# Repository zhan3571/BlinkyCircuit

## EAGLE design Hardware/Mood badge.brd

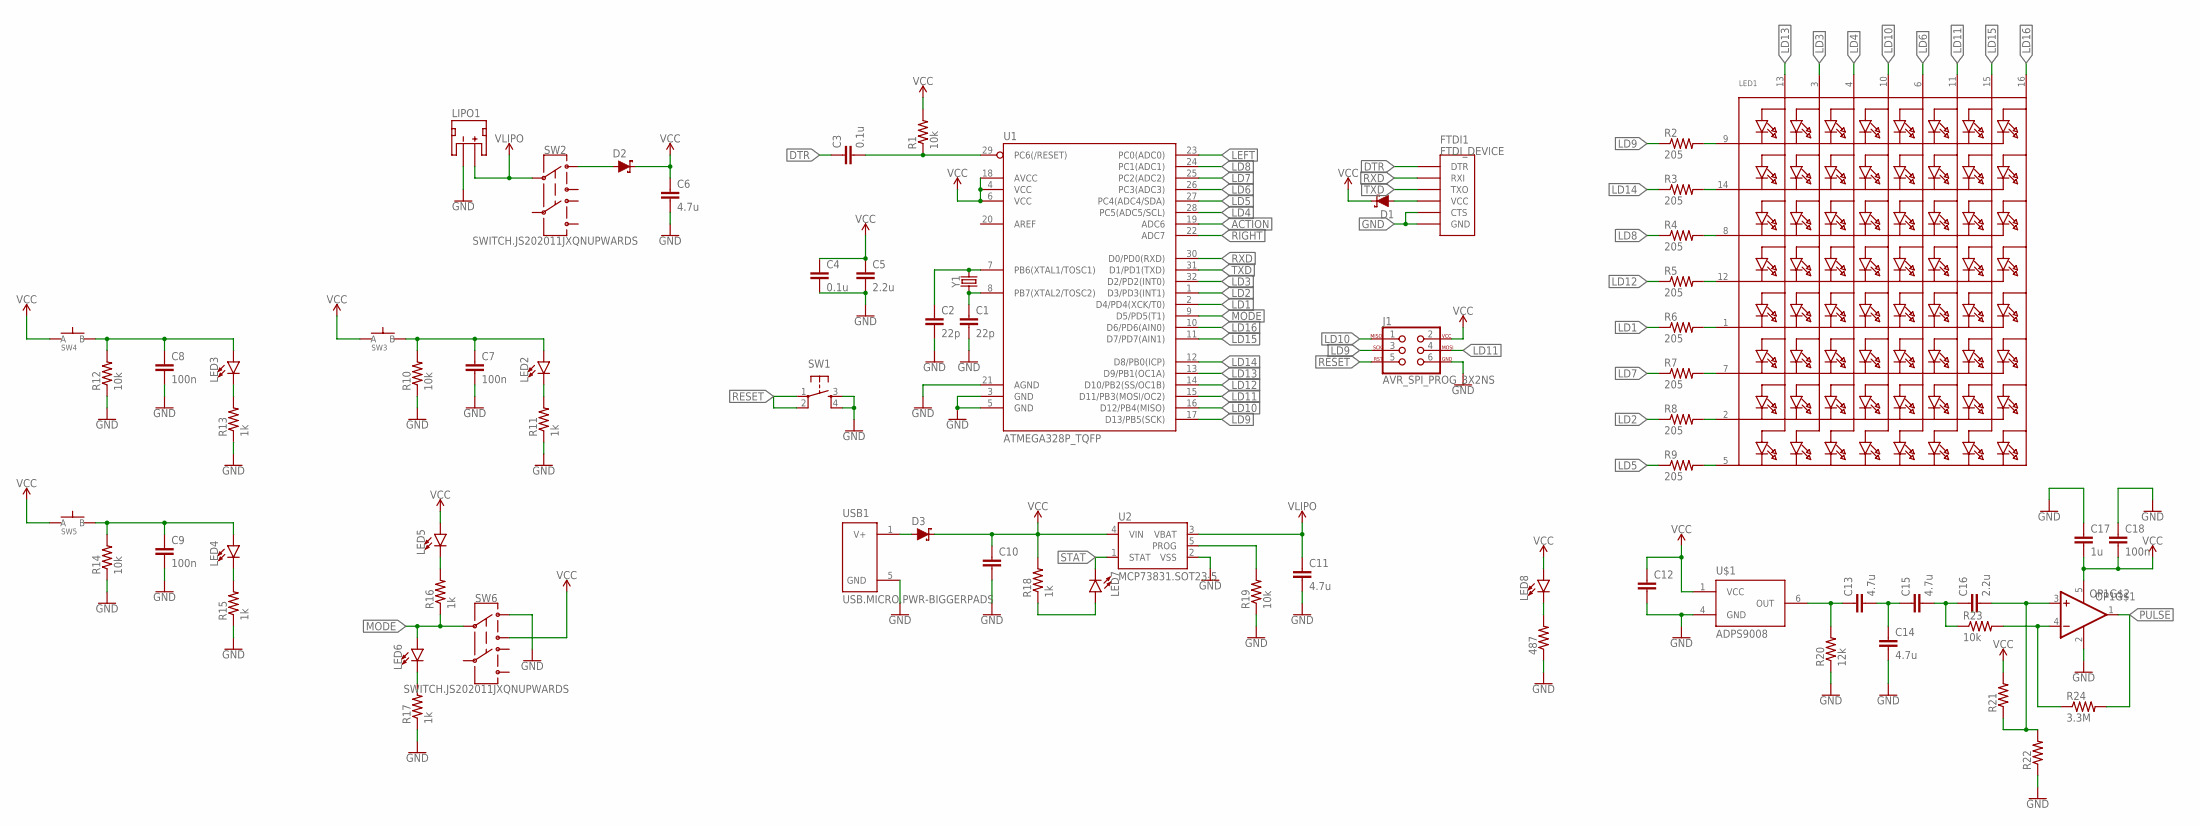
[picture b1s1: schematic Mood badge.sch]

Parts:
487: RESISTOR0603; R0603
C1, C2: 22p; C0603
C3, C4: 0.1u; C0603
C5, C16: 2.2u; C0603
C6, C11, C13, C14, C15: 4.7u; C0603
C7, C8, C9, C18: 100n; C0603
C10, C12: CAPACITOR0603; C0603
C17: 1u; C0603
D1, D2, D3: SCHOTTKY-USC; USC
FTDI1: FTDI_DEVICE
J1: AVR_SPI_PROG_3X2NS; 2X3-NS
LED1: SEGMENT_8X8_ROWCATHODEM12A881UR; SEGMENT_BL-M12A881UR
LED2, LED3, LED4, LED5, LED6, LED7, LED8: LED0603; LED-0603
LIPO1: JST_2MM_MALE; JST-2-SMD
OP1: OP-SINGLEOT; SOT23-5
R1, R10, R12, R14, R19, R23: 10k; R0603
R2, R3, R4, R5, R6, R7, R8, R9: 205; R0603
R11, R13, R15, R16, R17, R18: 1k; R0603
R20: 12k; R0603
R21, R22: RESISTOR0603; R0603
R24: 3.3M; R0603
SW1: SPST-PTS830GG140; BUTTON-GULLWING
SW2, SW6: SWITCH.JS202011JXQNUPWARDS; SWITCH.00
SW3, SW4, SW5: SPST.KT11P4SM34LFS
U1: ATMEGA328P_TQFP; TQFP32-08
U2: MCP73831.SOT23-5; SOT23-5
U$1: ADPS9008; 6-PIN.CHIPLED
USB1: USB.MICRO.PWR-BIGGERPADS; USB-MICRO-01.BIGGERPADS.PWR
Y1: CRYSTAL-CA-310; CA-301

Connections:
ACTION: U1.19 (ADC6)
DTR: C3.1, FTDI1.DTR
GND: 487.1, C1.2, C2.2, C4.2, C5.2, C6.2, C7.2, C8.2, C9.2, C10.2, C11.2, C12.2, C14.2, C17.1, C18.1, FTDI1.CTS, FTDI1.GND, J1.6, LIPO1.1 (-), OP1.2 (V-), R11.1, R13.1, R15.1, R17.1, R19.1, R20.1, R22.1, SW1.3, SW1.4, SW6.1, U1.3 (GND), U1.5 (GND), U1.21 (AGND), U2.2 (VSS), U$1.4 (GND), USB1.5 (GND)
LD1: R6.1, U1.2 (D4/PD4(XCK/T0))
LD2: R8.1, U1.1 (D3/PD3(INT1))
LD3: LED1.3 (A2), U1.32 (D2/PD2(INT0))
LD4: LED1.4 (A3), U1.28 (PC5(ADC5/SCL))
LD5: R9.1, U1.27 (PC4(ADC4/SDA))
LD6: LED1.6 (A5), U1.26 (PC3(ADC3))
LD7: R7.1, U1.25 (PC2(ADC2))
LD8: R4.1, U1.24 (PC1(ADC1))
LD9: J1.3, R2.1, U1.17 (D13/PB5(SCK))
LD10: J1.1, LED1.10 (A4), U1.16 (D12/PB4(MISO))
LD11: J1.4, LED1.11 (A6), U1.15 (D11/PB3(MOSI/OC2))
LD12: R5.1, U1.14 (D10/PB2(SS/OC1B))
LD13: LED1.13 (A1), U1.13 (D9/PB1(OC1A))
LD14: R3.1, U1.12 (D8/PB0(ICP))
LD15: LED1.15 (A7), U1.11 (D7/PD7(AIN1))
LD16: LED1.16 (A8), U1.10 (D6/PD6(AIN0))
LEFT: U1.23 (PC0(ADC0))
MODE: LED6.A, R16.1, SW6.2, U1.9 (D5/PD5(T1))
unnamed: C1.1, U1.8 (PB7(XTAL2/TOSC2)), Y1.1
unnamed: C2.1, U1.7 (PB6(XTAL1/TOSC1)), Y1.2
unnamed: C3.2, R1.1, U1.29 (PC6(/RESET))
unnamed: LED1.9 (K1), R2.2
unnamed: LED1.14 (K2), R3.2
unnamed: LED1.8 (K3), R4.2
unnamed: LED1.12 (K4), R5.2
unnamed: LED1.1 (K5), R6.2
unnamed: D1.+ (A), FTDI1.VCC
unnamed: LED1.7 (K6), R7.2
unnamed: LED1.2 (K7), R8.2
unnamed: LED1.5 (K8), R9.2
unnamed: D2.+ (A), SW2.1
unnamed: LIPO1.2 (+), SW2.2
unnamed: C8.1, LED3.A, R12.2, SW4.3 (B), SW4.4 (B)
unnamed: C7.1, LED2.A, R10.2, SW3.3 (B), SW3.4 (B)
unnamed: R10.1, R12.1, R14.1
unnamed: LED3.C, R13.2
unnamed: LED2.C, R11.2
unnamed: C9.1, LED4.A, R14.2, SW5.3 (B), SW5.4 (B)
unnamed: LED4.C, R15.2
unnamed: LED6.C, R17.2
unnamed: LED5.C, R16.2
unnamed: D3.+ (A), USB1.1 (V+)
unnamed: 487.2, LED8.C
unnamed: LED7.A, R18.1
unnamed: R19.2, U2.5 (PROG)
unnamed: C15.2, C16.1, R23.1
unnamed: C16.2, OP1.3 (+IN), R21.1, R22.2
unnamed: C13.1, R20.2, U$1.6 (OUT)
unnamed: C13.2, C14.1, C15.1
unnamed: OP1.4 (-IN), R23.2, R24.1
PULSE: OP1.1 (OUT), R24.2
RESET: J1.5, SW1.1, SW1.2
RIGHT: U1.22 (ADC7)
RXD: FTDI1.TXO (RXI), U1.30 (D0/PD0(RXD))
STAT: LED7.C, U2.1 (STAT)
TXD: FTDI1.RXI (TXO), U1.31 (D1/PD1(TXD))
VCC: C4.1, C5.1, C6.1, C10.1, C12.1, C17.2, C18.2, D1.- (C), D2.- (C), D3.- (C), J1.2, LED5.A, LED8.A, OP1.5 (V+), R1.2, R18.2, R21.2, SW3.1 (A), SW3.2 (A), SW4.1 (A), SW4.2 (A), SW5.1 (A), SW5.2 (A), SW6.3, U1.4 (VCC), U1.6 (VCC), U1.18 (AVCC), U2.4 (VIN), U$1.1 (VCC)
VLIPO: C11.1, U2.3 (VBAT)

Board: 2 copper layers, 69 parts (0 on the bottom side), 58 nets, no tracks yet.

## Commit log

2021-02-20 word doc description
2021-02-20 shape idea
2021-02-20 organized
2021-02-20 rough sketch
2021-02-20 schem and board added
2021-03-06 microcontroller
2021-03-15 schematic done
2021-03-15 board of schem
2021-03-20 board start
2021-03-20 board starting
